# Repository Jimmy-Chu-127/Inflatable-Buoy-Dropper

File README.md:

# Inflatable Buoy Dropper

### Webpage
https://sites.google.com/ucsd.edu/littlefrog/home?authuser=1

### Demo Video
[](https://youtu.be/II8ibG0zH5Y
"Inflatable Buoy Dropper")

### Objective:
This device is intended to be a drone attachment that can be dropped to drowning victim and inflate upon detecting water.

### Functional Description:
1. Long range dropping control through ESP32 Lora
2. Water sensor to automatically initiate inflation upon hitting water

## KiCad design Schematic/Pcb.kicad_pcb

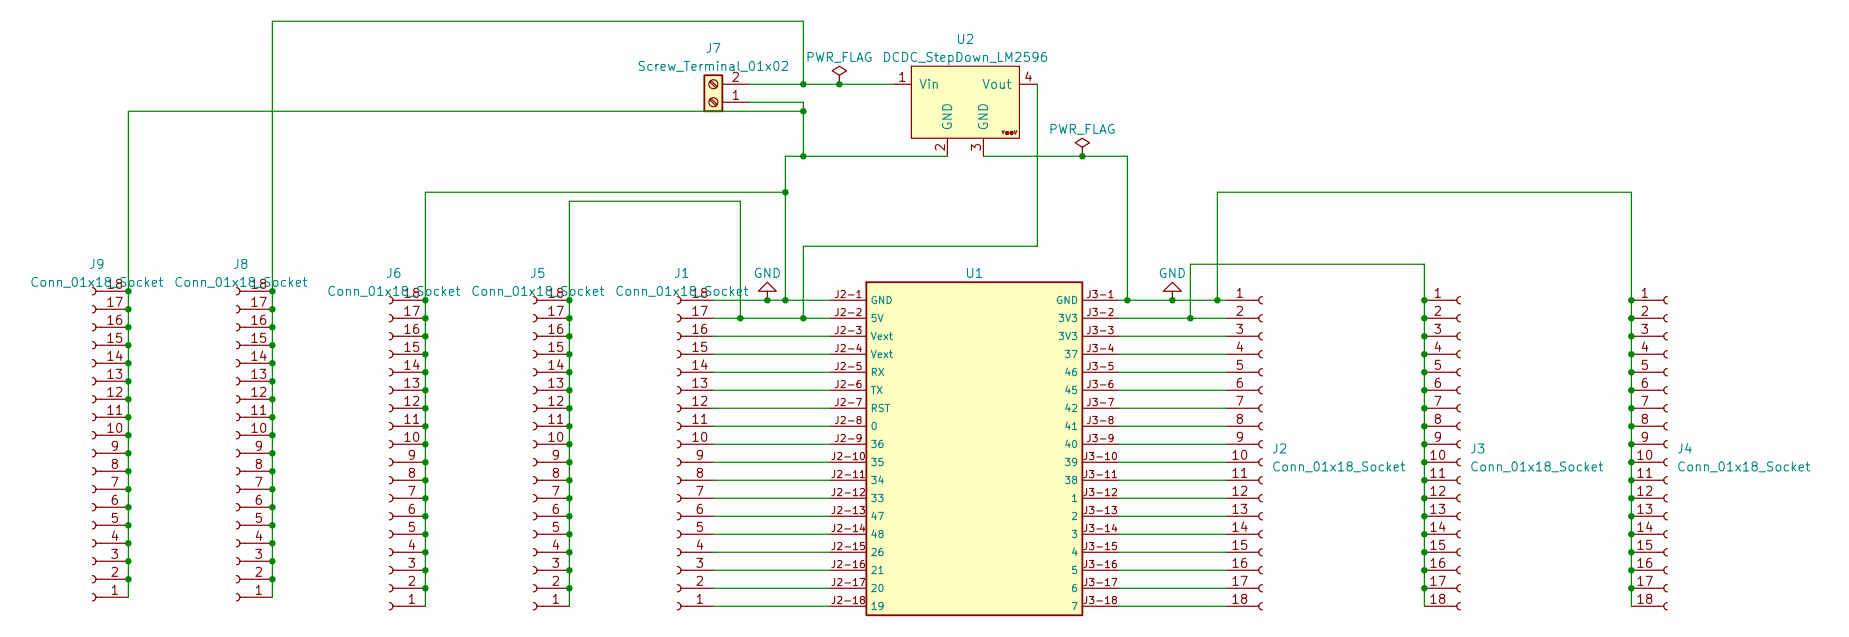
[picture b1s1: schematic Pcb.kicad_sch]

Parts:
J1, J2, J3, J4, J5, J6, J8, J9: Conn_01x18_Socket; PinSocket_1x18_P2.54mm_Vertical
J7: Screw_Terminal_01x02; TerminalBlock_Altech_AK300-2_P5.00mm
U1: esp32Lora_foot_Print
U2: DCDC_StepDown_LM2596

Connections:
GND: J1.18, J2.1, J4.1, J4.2, J4.3, J4.4, J4.5, J4.6, J4.7, J4.8, J4.9, J4.10, J4.11, J4.12, J4.13, J4.14, J4.15, J4.16, J4.17, J4.18, J6.1, J6.2, J6.3, J6.4, J6.5, J6.6, J6.7, J6.8, J6.9, J6.10, J6.11, J6.12, J6.13, J6.14, J6.15, J6.16, J6.17, J6.18, J7.1, J9.1, J9.2, J9.3, J9.4, J9.5, J9.6, J9.7, J9.8, J9.9, J9.10, J9.11, J9.12, J9.13, J9.14, J9.15, J9.16, J9.17, J9.18, U1.J2-1 (GND), U1.J3-1 (GND), U2.2 (GND), U2.3 (GND)
unnamed: J1.1, U1.J2-18 (19)
unnamed: J1.2, U1.J2-17 (20)
unnamed: J1.3, U1.J2-16 (21)
unnamed: J1.4, U1.J2-15 (26)
unnamed: J1.5, U1.J2-14 (48)
unnamed: J1.6, U1.J2-13 (47)
unnamed: J1.7, U1.J2-12 (33)
unnamed: J1.8, U1.J2-11 (34)
unnamed: J1.9, U1.J2-10 (35)
unnamed: J1.10, U1.J2-9 (36)
unnamed: J1.11, U1.J2-8 (0)
unnamed: J1.12, U1.J2-7 (RST)
unnamed: J1.13, U1.J2-6 (TX)
unnamed: J1.14, U1.J2-5 (RX)
unnamed: J1.15, U1.J2-4 (Vext)
unnamed: J1.16, U1.J2-3 (Vext)
unnamed: J1.17, J5.1, J5.2, J5.3, J5.4, J5.5, J5.6, J5.7, J5.8, J5.9, J5.10, J5.11, J5.12, J5.13, J5.14, J5.15, J5.16, J5.17, J5.18, U1.J2-2 (5V), U2.4 (Vout)
unnamed: J2.2, J3.1, J3.2, J3.3, J3.4, J3.5, J3.6, J3.7, J3.8, J3.9, J3.10, J3.11, J3.12, J3.13, J3.14, J3.15, J3.16, J3.17, J3.18, U1.J3-2 (3V3)
unnamed: J2.3, U1.J3-3 (3V3)
unnamed: J2.4, U1.J3-4 (37)
unnamed: J2.5, U1.J3-5 (46)
unnamed: J2.6, U1.J3-6 (45)
unnamed: J2.7, U1.J3-7 (42)
unnamed: J2.8, U1.J3-8 (41)
unnamed: J2.9, U1.J3-9 (40)
unnamed: J2.10, U1.J3-10 (39)
unnamed: J2.11, U1.J3-11 (38)
unnamed: J2.12, U1.J3-12 (1)
unnamed: J2.13, U1.J3-13 (2)
unnamed: J2.14, U1.J3-14 (3)
unnamed: J2.15, U1.J3-15 (4)
unnamed: J2.16, U1.J3-16 (5)
unnamed: J2.17, U1.J3-17 (6)
unnamed: J2.18, U1.J3-18 (7)
unnamed: J7.2, J8.1, J8.2, J8.3, J8.4, J8.5, J8.6, J8.7, J8.8, J8.9, J8.10, J8.11, J8.12, J8.13, J8.14, J8.15, J8.16, J8.17, J8.18, U2.1 (Vin)

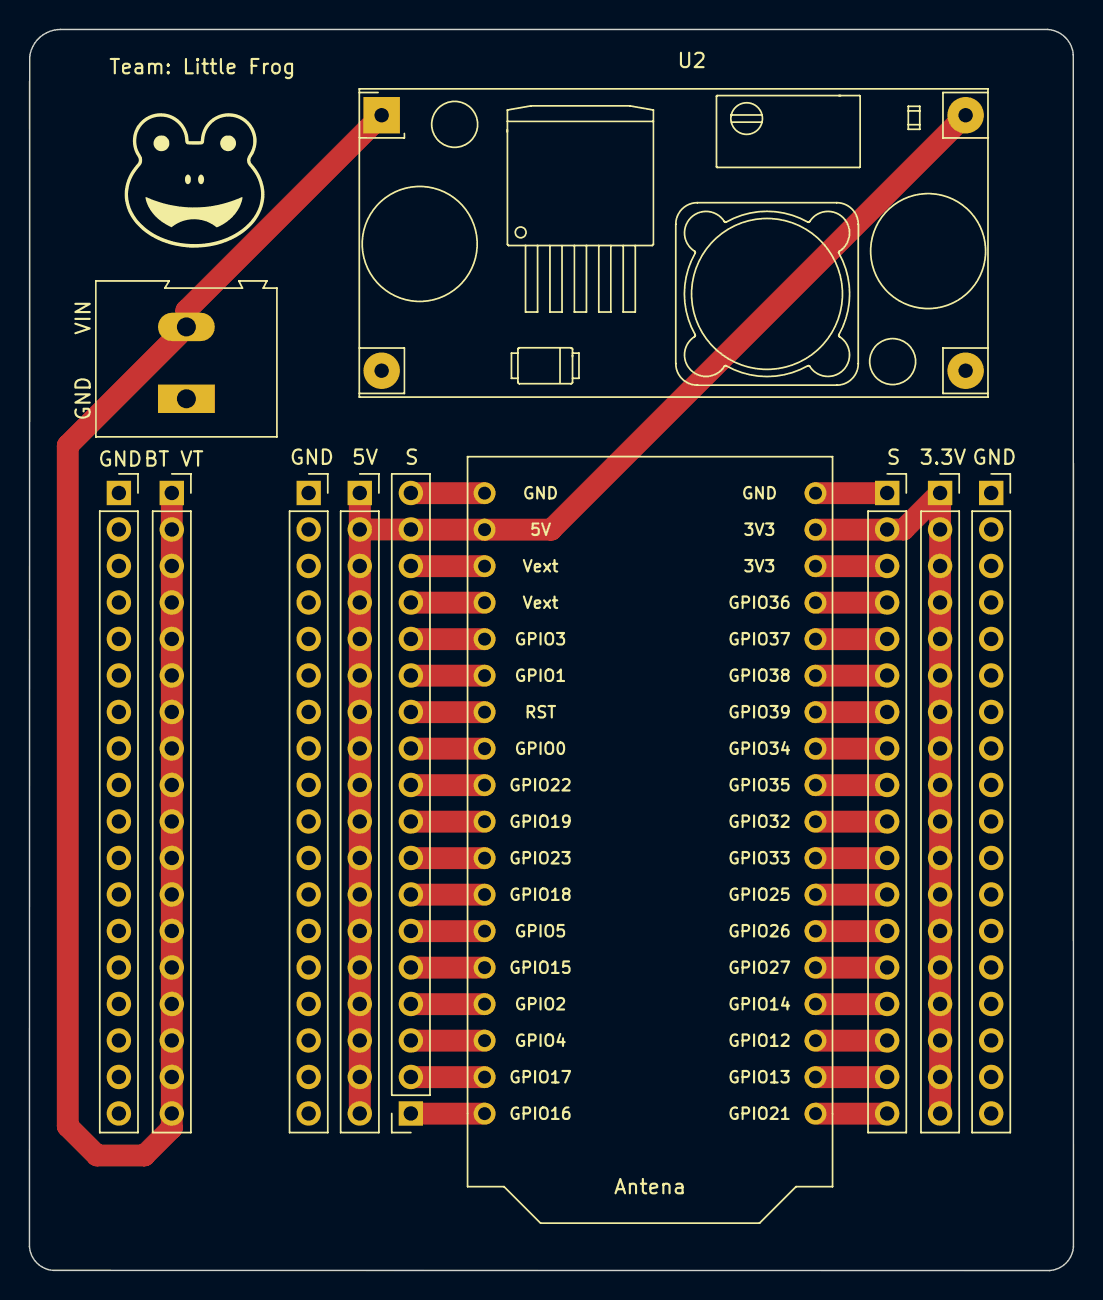
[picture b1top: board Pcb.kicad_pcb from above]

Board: 2 copper layers, 72.7 x 86.4 mm, 11 parts (0 on the bottom side), 36 nets.

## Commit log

2023-05-02 servo+attachment
2023-05-04 dropping mechanism update
2023-05-04 dimension adjustments
2023-05-11 whole assem update
2023-05-13 3D printing slicing
2023-05-13 G code clearance modification
2023-05-21 whole mechanism update
2023-05-24 PCB enclosure update
2023-05-25 New PCB enclosure design, whole assembly inclusion
2023-05-25 3D printing files update
2023-05-25 PCB enclosure and whole assembly update
2023-05-26 small update
2023-05-26 PCB enclosure 3D printing file update
2023-06-03 Rename OLED_LoRa_Receiver.ino to Receiver_code.ino
2023-06-03 Rename OLED_LoRa_Sender.ino to Sender_code.ino
2023-07-30 Organizing file structure
2023-07-30 README update
2023-07-30 Creating image folder
